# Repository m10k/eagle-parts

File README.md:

# eagle-parts

This is a library of various EAGLE parts that I have created along the way of my projects. Unless stated otherwise,
the footprints included in this library are untested. Double-check them if you wish to include them in your own projects.

Parts in this library:

* Bosch BNO055 IMU (28-pin LGA package)
* Microchip SAM C21G18A (48-pin QFN package)

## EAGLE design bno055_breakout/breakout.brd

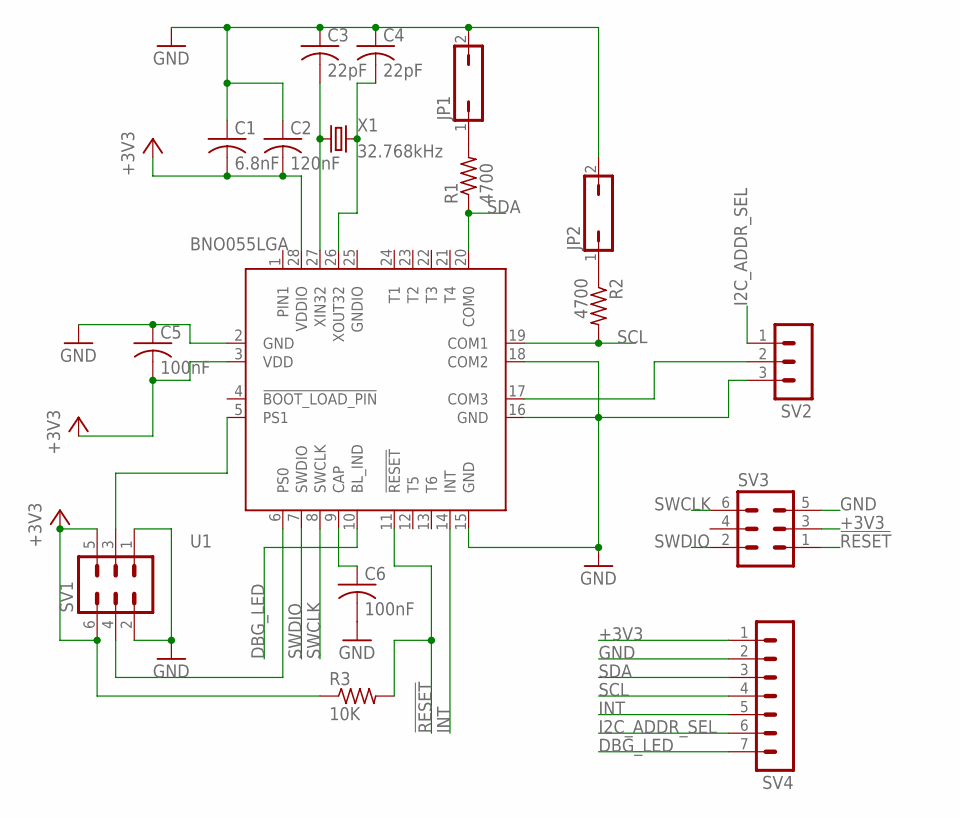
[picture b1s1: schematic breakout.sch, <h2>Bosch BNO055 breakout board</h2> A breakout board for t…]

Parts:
C1: 6.8nF; C0805
C2: 120nF; C0805
C3, C4: 22pF; C0805
C5, C6: 100nF; C0805
JP1, JP2: JP1Q; JP1
R1, R2: 4700; R0805
R3: 10K; R0805
SV1, SV3: MA03-2
SV2: MA03-1
SV4: MA07-1
U1: BNO055LGA; LGA28_BOSCH
X1: 32.768kHz; WATCH-3X8

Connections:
!RESET: R3.2, SV3.1, U1.11 (!RESET)
+3V3: C1.2, C2.2, C5.2, R3.1, SV1.5, SV1.6, SV3.3, SV4.1, U1.3 (VDD), U1.28 (VDDIO)
DBG_LED: SV4.7, U1.10 (BL_IND)
GND: C1.1, C2.1, C3.1, C4.1, C5.1, C6.2, JP1.2, JP2.2, SV1.1, SV1.2, SV2.3, SV3.5, SV4.2, U1.2 (GND), U1.15 (GND), U1.16 (GND), U1.18 (COM2)
GNDIO: U1.25 (GNDIO)
I2C_ADDR_SEL: SV2.1, SV4.6
INT: SV4.5, U1.14 (INT)
unnamed: C3.2, U1.27 (XIN32), X1.1
unnamed: C4.2, U1.26 (XOUT32), X1.2
unnamed: JP1.1, R1.2
unnamed: JP2.1, R2.1
unnamed: SV2.2, U1.17 (COM3)
unnamed: C6.1, U1.9 (CAP)
unnamed: SV1.3, U1.5 (PS1)
unnamed: SV1.4, U1.6 (PS0)
SCL: R2.2, SV4.4, U1.19 (COM1)
SDA: R1.1, SV4.3, U1.20 (COM0)
SWCLK: SV3.6, U1.8 (SWCLK)
SWDIO: SV3.2, U1.7 (SWDIO)

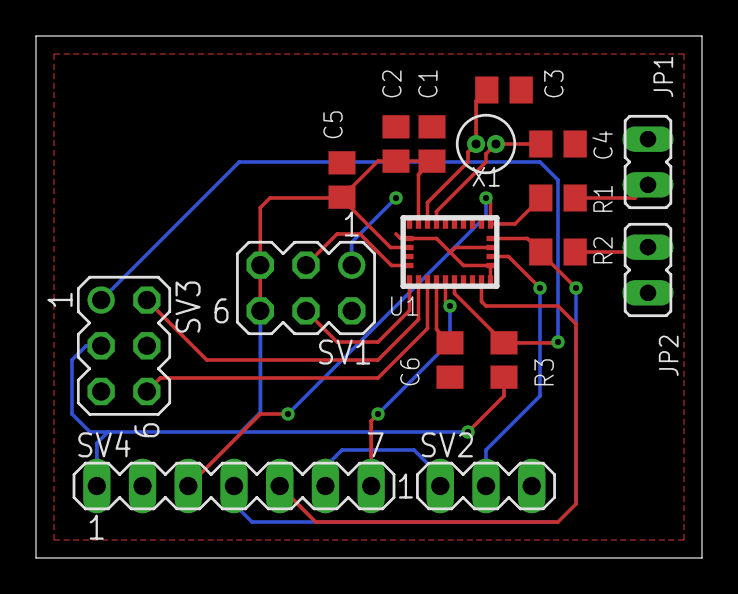
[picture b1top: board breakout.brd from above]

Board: 2 copper layers, 37.0 x 29.0 mm, 17 parts (0 on the bottom side), 18 nets.

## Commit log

2017-07-20 Add Bosch BNO055 and Microchip SAMC21G18A
2017-08-09 Add breakout board for Bosch BNO055 9-DOF IMU
